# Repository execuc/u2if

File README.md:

# u2if project

u2if(USB to interfaces) is an attempt to implement some of the MicroPython "machine" module functionalities on a computer.
The goal is to be able to communicate with breakout boards (sensors, lcd...) simply from a python program on x86 machine. It uses a Raspberry PICO (or other RP2040 based board) to make the interface between the computer (USB) and peripherals/protocols.

**Python led swith on/off**:
```python
import time
from machine import u2if, Pin

# Initialize GPIO to output and set the value HIGH
led = Pin(u2if.GP3, Pin.OUT, value=Pin.HIGH)
time.sleep(1)
# Switch off the led
led.value(Pin.LOW)
```

## Caution

It is in experimental state and not everything has been tested. Use with caution. It is supposed to work on windows, linux and Mac.
To work in Linux in non-root, an udev rules has to be added (See [Firmware readme](firmware/README.md)).

## Why this project ?
When I want to retrieve values from a sensor or even to play with a led or a button from the PC, I make an arduino program that communicate to the PC via the serial port. That umplies to define a serial "protocol" between the PC and the arduino and it is not necessarily reusable because it is specific. I find it interesting to implement a majority of the functionalities of the MicroPython machine module and add other protocols.

Solutions already exist, for example [Adafruit Blinka](https://github.com/adafruit/Adafruit_Blinka) from Adafruit via the FT2232H in CircuitPython or pyftdi in Python with the same IC.
Note: now, firmware part can be also used with Adafruit Blinka ! 

## Implemented Interfaces
The following features are coded:

* machine.Pin: input (+irq, +debounced), output (+pull down/up) and grouped pins.
* machine.Signal
* machine.ADC: read (12bits)
* machine.UART
* machine.I2C
* machine.SPI
* machine.PWM
* I2S
* WS2812B led (https://youtu.be/WCGI4C6nZ-o)
* HUB75 (https://youtu.be/qRShI9y964Q)

## Licenses and Project directories
This repository is presented as the sources of a python project ([License](source/LICENSE)).
But it also contains the following projects:

 * [firmware](firmware/): PICO firmware, binary and C++ source [License](firmware/source/LICENSE).
 * [examples](examples/): Python program examples.
 * [board](board/): Example of a pico headers board for this project  ([License](firmware/source/LICENSE)).

## How to use it

### Upload firmware
See [Firmware README](firmware/README.md)

### Install u2if python package

Install python package from release file (u2if-*.*.tar.gz) with python3 -m pip install dist/u2if-*.*.tar.gz

## Build u2if python package

To build package if wanted :

 * If needed, install build: python3 -m pip install --upgrade build
 * Build it: python3 -m build

### Examples

There is no documentation but [examples](examples/) can help to use this library :

 * Led On/Off
 * Switch with or whithour irq and debouncing
 * PWM controlling servo-motor
 * Display testing: SSD1306 (I2C and SPI), GC9A01 (round lcd)
 * Some sensors simple test: MPU9250 (IMU), VL53L0X (range), BMP280(Temp)
 * UART read/Write
 * Analog read.
 * Rotrary encoder
 * I2C scan
 * Play 48khz 16bit .wav over I2S DAC (PAM5102)
 * ...

## u2if boards/pinout

For simplicity, the pins of the SPI, I2C and UART devices have been fixed. If a peripheral is not used, its pins can be used as a classic I/O. Here are the compatibles boards.

### PICO
<details>

Implemented interfaces:
 - GPIO
 - ADC
 - PWM
 - UART0 & UART1
 - I2C0 & I2C1
 - SPI0 & SPI1
 - WS2812B
 - I2S

</details>

### Adafruit Feather RP2040
<details>

Implemented interfaces:
 - GPIO
 - ADC
 - PWM
 - UART0
 - I2C0 & I2C1
 - SPI0 & SPI1
 - WS2812B

</details>

### Adafruit Qt Py RP2040
<details>

Implemented interfaces:
 - GPIO
 - ADC
 - PWM
 - UART1
 - I2C0 & I2C1
 - SPI0
 - WS2812B

</details>

### Adafruit ItsyBitsy RP2040
<details>

Implemented interfaces:
 - GPIO
 - ADC
 - PWM
 - UART0
 - I2C1
 - SPI0 & SPI1
 - WS2812B

</details>

### Adafruit MacroPad RP2040
<details>

Implemented interfaces:
 - GPIO
 - PWM
 - UART1
 - I2C0
 - SPI1
 - WS2812B

</details>

### Adafruit Trinkey QT2040
<details>

Implemented interfaces:
 - GPIO
 - ADC
 - PWM
 - UART0
 - I2C0 & I2C1
 - SPI0 & SPI1
 - WS2812B

</details>

## Troubleshooting
### Import error using MicroPython module
#### import ustruct

The ustruct module is belongs by micropython. There is a micropython-cpython-ustruct compatibility module, but it doesn't seem to work for me. If necessary modify:
```python
import ustruct
```
to:
```python
import struct as ustruct
```

#### import utime & const

Install micropython-cpython-utime and micropython-cpython-micropython.

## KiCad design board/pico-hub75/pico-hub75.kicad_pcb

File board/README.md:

# PICO headers dev board

There are some kicad projects of a PCB with some I/O but mostly headers.
**Caution**: I am not an electronic engineer, check schematics and PCB before using it !

## pico-dev-v2
Dev. board with headers.

Zipped gerber file is available: [Gerber file](pico-dev/gerber/pico-dev-v2.zip)

## pico-dev-hub75
Dev. board with hub75 connector. Caution, there is no level translator (3.3v -> 5V), so it may not work with some leds matrix because of they work on 5V logic level.

There are two jumpers to wire D and E signal in case of 1/16 and 1/32 panels.

Zipped gerber file is available: [Gerber file](pico-hub75/gerber/pico-hub75.zip)

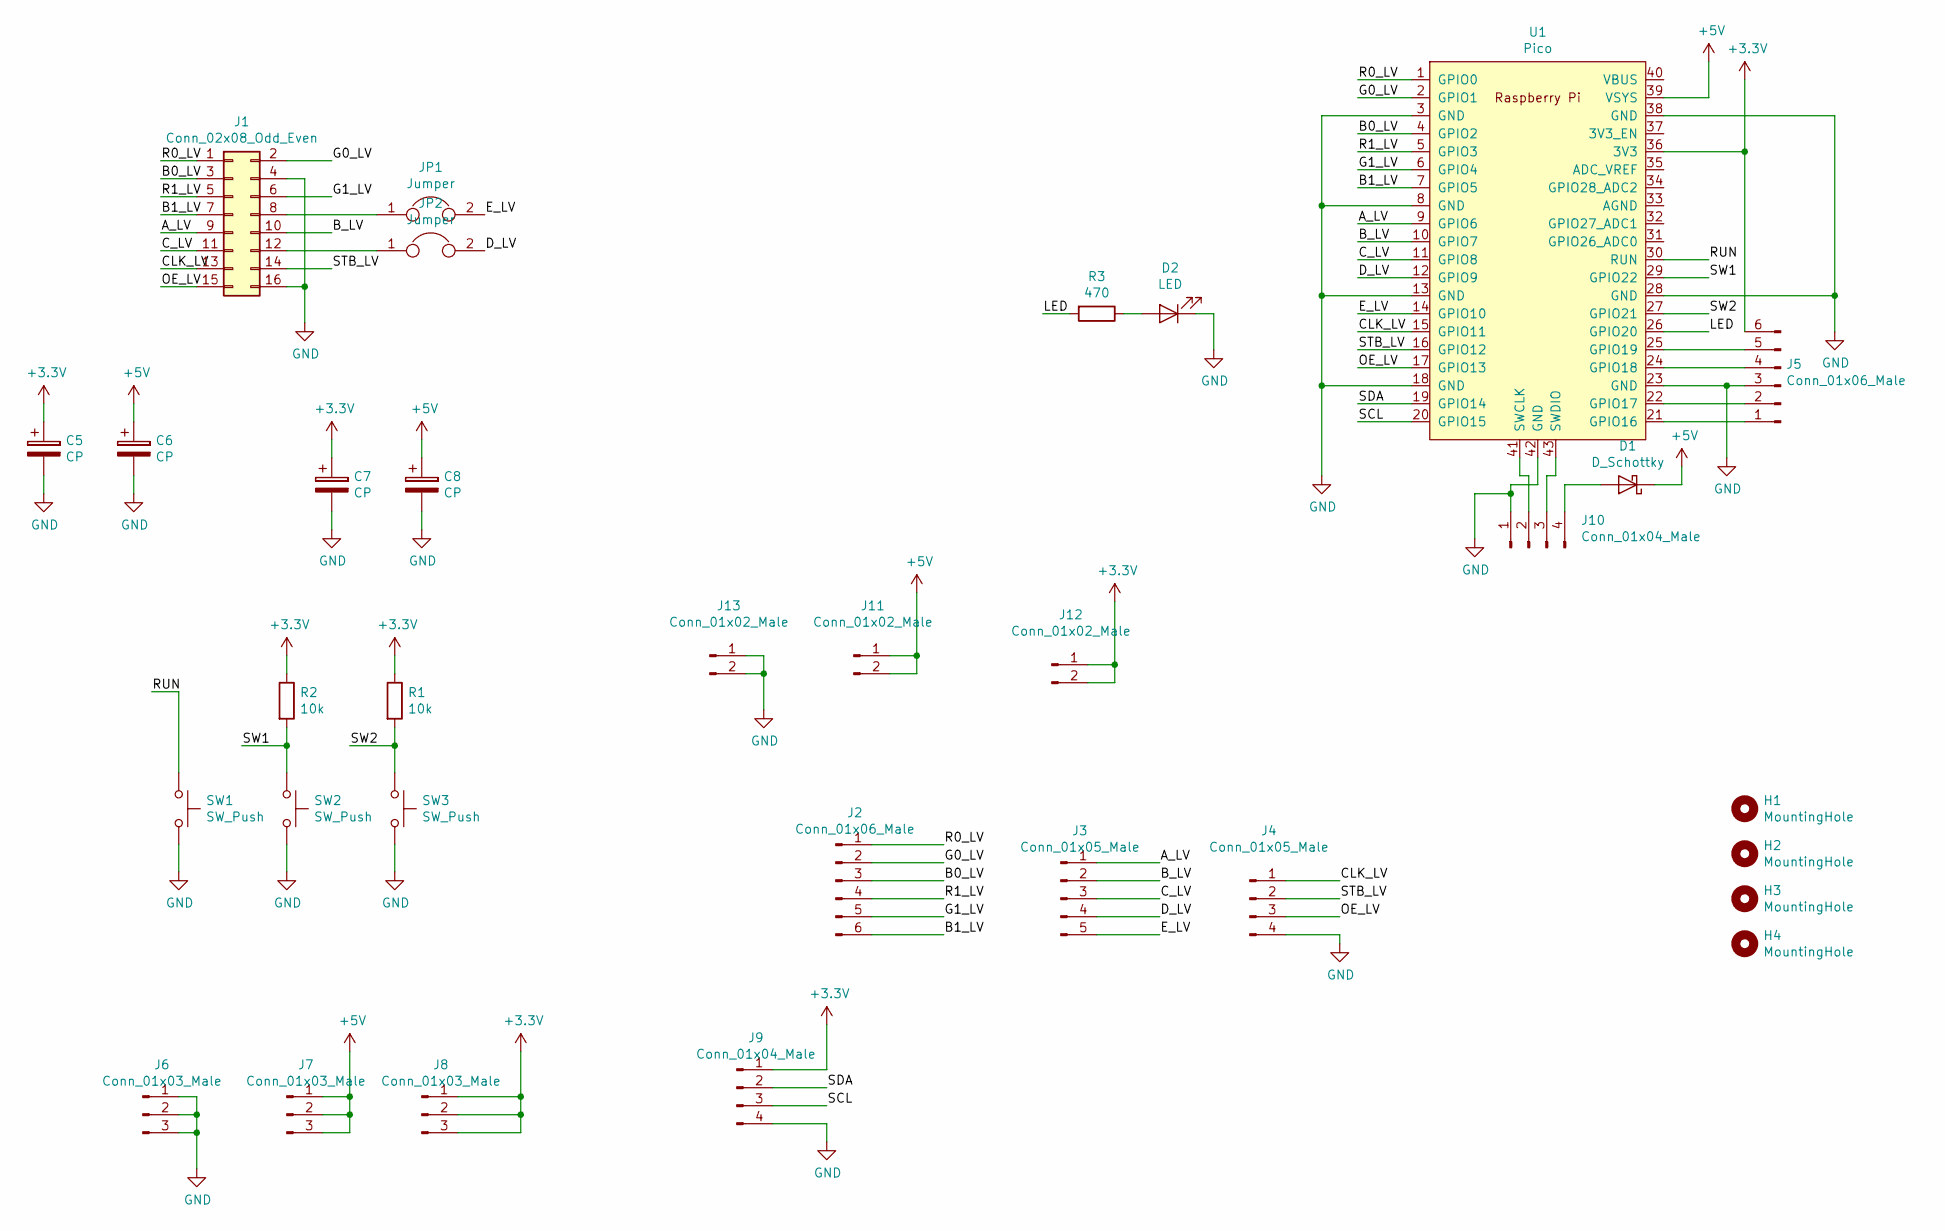
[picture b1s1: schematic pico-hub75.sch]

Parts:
C5, C6, C7, C8: CP; CP_Radial_D6.3mm_P2.50mm
D1: D_Schottky; D_SMA
D2: LED; LED_1206_3216Metric_Pad1.42x1.75mm_HandSolder; LCSC C2296
H1, H2, H3, H4: MountingHole; MountingHole_3.2mm_M3
J1: Conn_02x08_Odd_Even; IDC-Header_2x08_P2.54mm_Vertical
J2, J5: Conn_01x06_Male; PinHeader_1x06_P2.54mm_Vertical
J3: Conn_01x05_Male; PinHeader_1x05_P2.54mm_Vertical
J4: Conn_01x05_Male; PinHeader_1x04_P2.54mm_Vertical
J6, J7, J8: Conn_01x03_Male; PinHeader_1x03_P2.54mm_Vertical
J9, J10: Conn_01x04_Male; PinHeader_1x04_P2.54mm_Vertical
J11, J12, J13: Conn_01x02_Male; PinHeader_1x02_P2.54mm_Vertical
JP1, JP2: Jumper; PinHeader_1x02_P2.54mm_Vertical
R1, R2: 10k; R_1206_3216Metric_Pad1.42x1.75mm_HandSolder; LCSC C17414
R3: 470; R_1206_3216Metric_Pad1.42x1.75mm_HandSolder; LCSC C17710
SW1, SW2, SW3: SW_Push; SW_PUSH_6mm_H5mm
U1: Pico; RPi_Pico_SMD_TH

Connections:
+3V3: C5.1, C7.1, J5.6, J8.1, J8.2, J8.3, J9.1, J12.1, J12.2, R1.1, R2.1, U1.36 (3V3); also elsewhere on the board
+5V: C6.1, C8.1, D1.1 (K), J7.1, J7.2, J7.3, J11.1, J11.2, U1.39 (VSYS); also elsewhere on the board
/A_LV: J1.9, J3.1, U1.9 (GPIO6)
/B0_LV: J1.3, J2.3, U1.4 (GPIO2)
/B1_LV: J1.7, J2.6, U1.7 (GPIO5)
/B_LV: J1.10, J3.2, U1.10 (GPIO7)
/CLK_LV: J1.13, J4.1, U1.15 (GPIO11)
/C_LV: J1.11, J3.3, U1.11 (GPIO8)
/D_LV: J3.4, JP2.2, U1.12 (GPIO9)
/E_LV: J3.5, JP1.2, U1.14 (GPIO10)
/G0_LV: J1.2, J2.2, U1.2 (GPIO1)
/G1_LV: J1.6, J2.5, U1.6 (GPIO4)
/LED: R3.2, U1.26 (GPIO20)
/OE_LV: J1.15, J4.3, U1.17 (GPIO13)
/R0_LV: J1.1, J2.1, U1.1 (GPIO0)
/R1_LV: J1.5, J2.4, U1.5 (GPIO3)
/RUN: SW1.1, U1.30 (RUN)
/SCL: J9.3, U1.20 (GPIO15)
/SDA: J9.2, U1.19 (GPIO14)
/STB_LV: J1.14, J4.2, U1.16 (GPIO12)
/SW1: R2.2, SW2.1, U1.29 (GPIO22)
/SW2: R1.2, SW3.1, U1.27 (GPIO21)
GND: C5.2, C6.2, C7.2, C8.2, D2.1 (K), J1.4, J1.16, J4.4, J5.3, J6.1, J6.2, J6.3, J9.4, J10.1, J13.1, J13.2, SW1.2, SW2.2, SW3.2, U1.3 (GND), U1.8 (GND), U1.13 (GND), U1.18 (GND), U1.23 (GND), U1.28 (GND), U1.38 (GND), U1.42 (GND); also elsewhere on the board
unnamed: D1.2 (A), J10.4
unnamed: D2.2 (A), R3.1
unnamed: J1.8, JP1.1
unnamed: J1.12, JP2.1
unnamed: J5.1, U1.21 (GPIO16)
unnamed: J5.2, U1.22 (GPIO17)
unnamed: J5.4, U1.24 (GPIO18)
unnamed: J5.5, U1.25 (GPIO19)
unnamed: J10.2, U1.41 (SWCLK)
unnamed: J10.3, U1.43 (SWDIO)

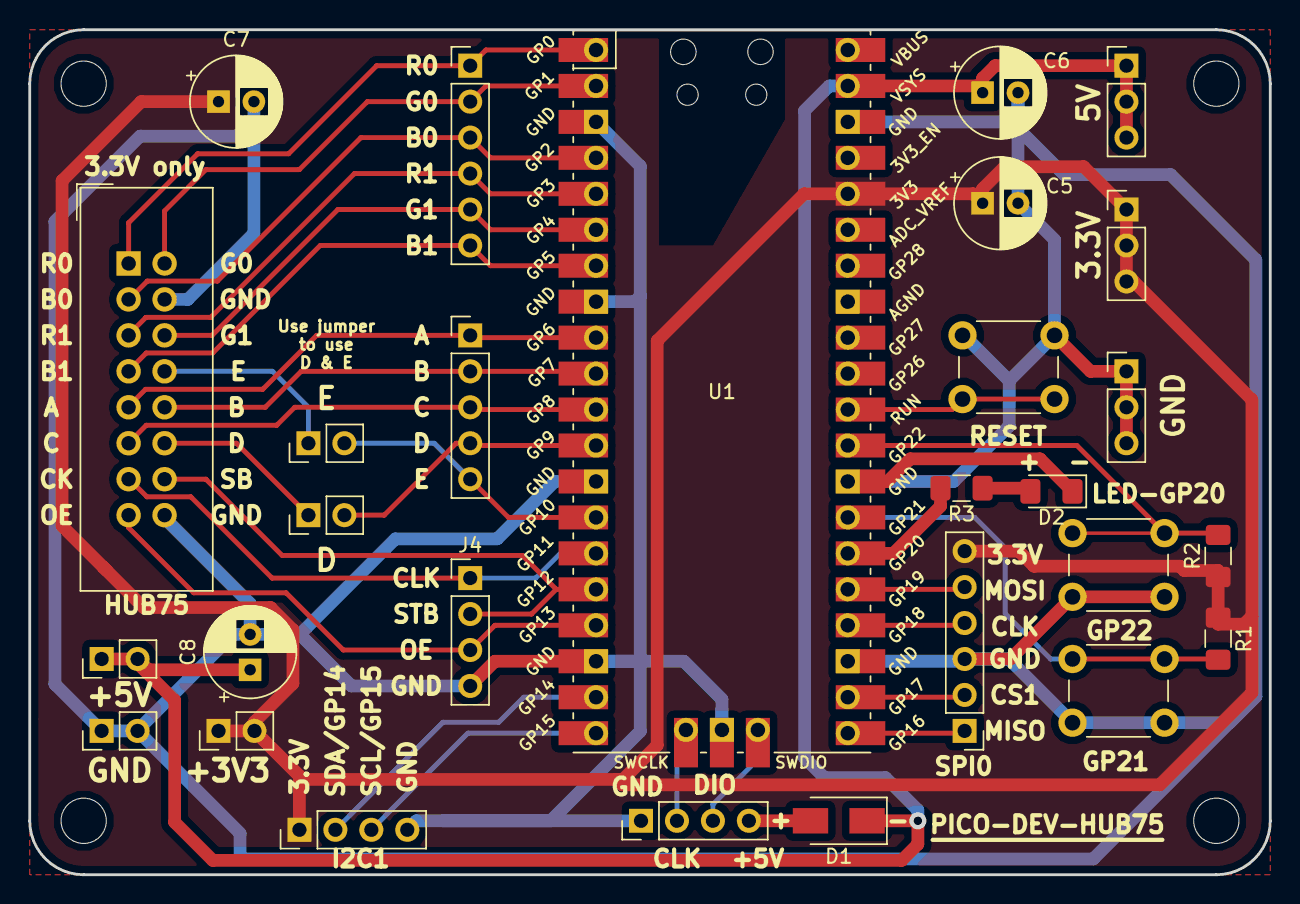
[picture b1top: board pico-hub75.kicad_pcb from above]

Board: 2 copper layers, 87.6 x 59.7 mm, 32 parts (0 on the bottom side), 33 nets.

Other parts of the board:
+3V3, +5V: Conn_01x02_Male; PinHeader_1x02_P2.54mm_Vertical
GND: Conn_01x02_Male; PinHeader_1x02_P2.54mm_Vertical

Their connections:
+3V3: +3V3.1, +3V3.2; also elsewhere on the board
+5V: +5V.1, +5V.2; also elsewhere on the board
GND: GND.1, GND.2; also elsewhere on the board

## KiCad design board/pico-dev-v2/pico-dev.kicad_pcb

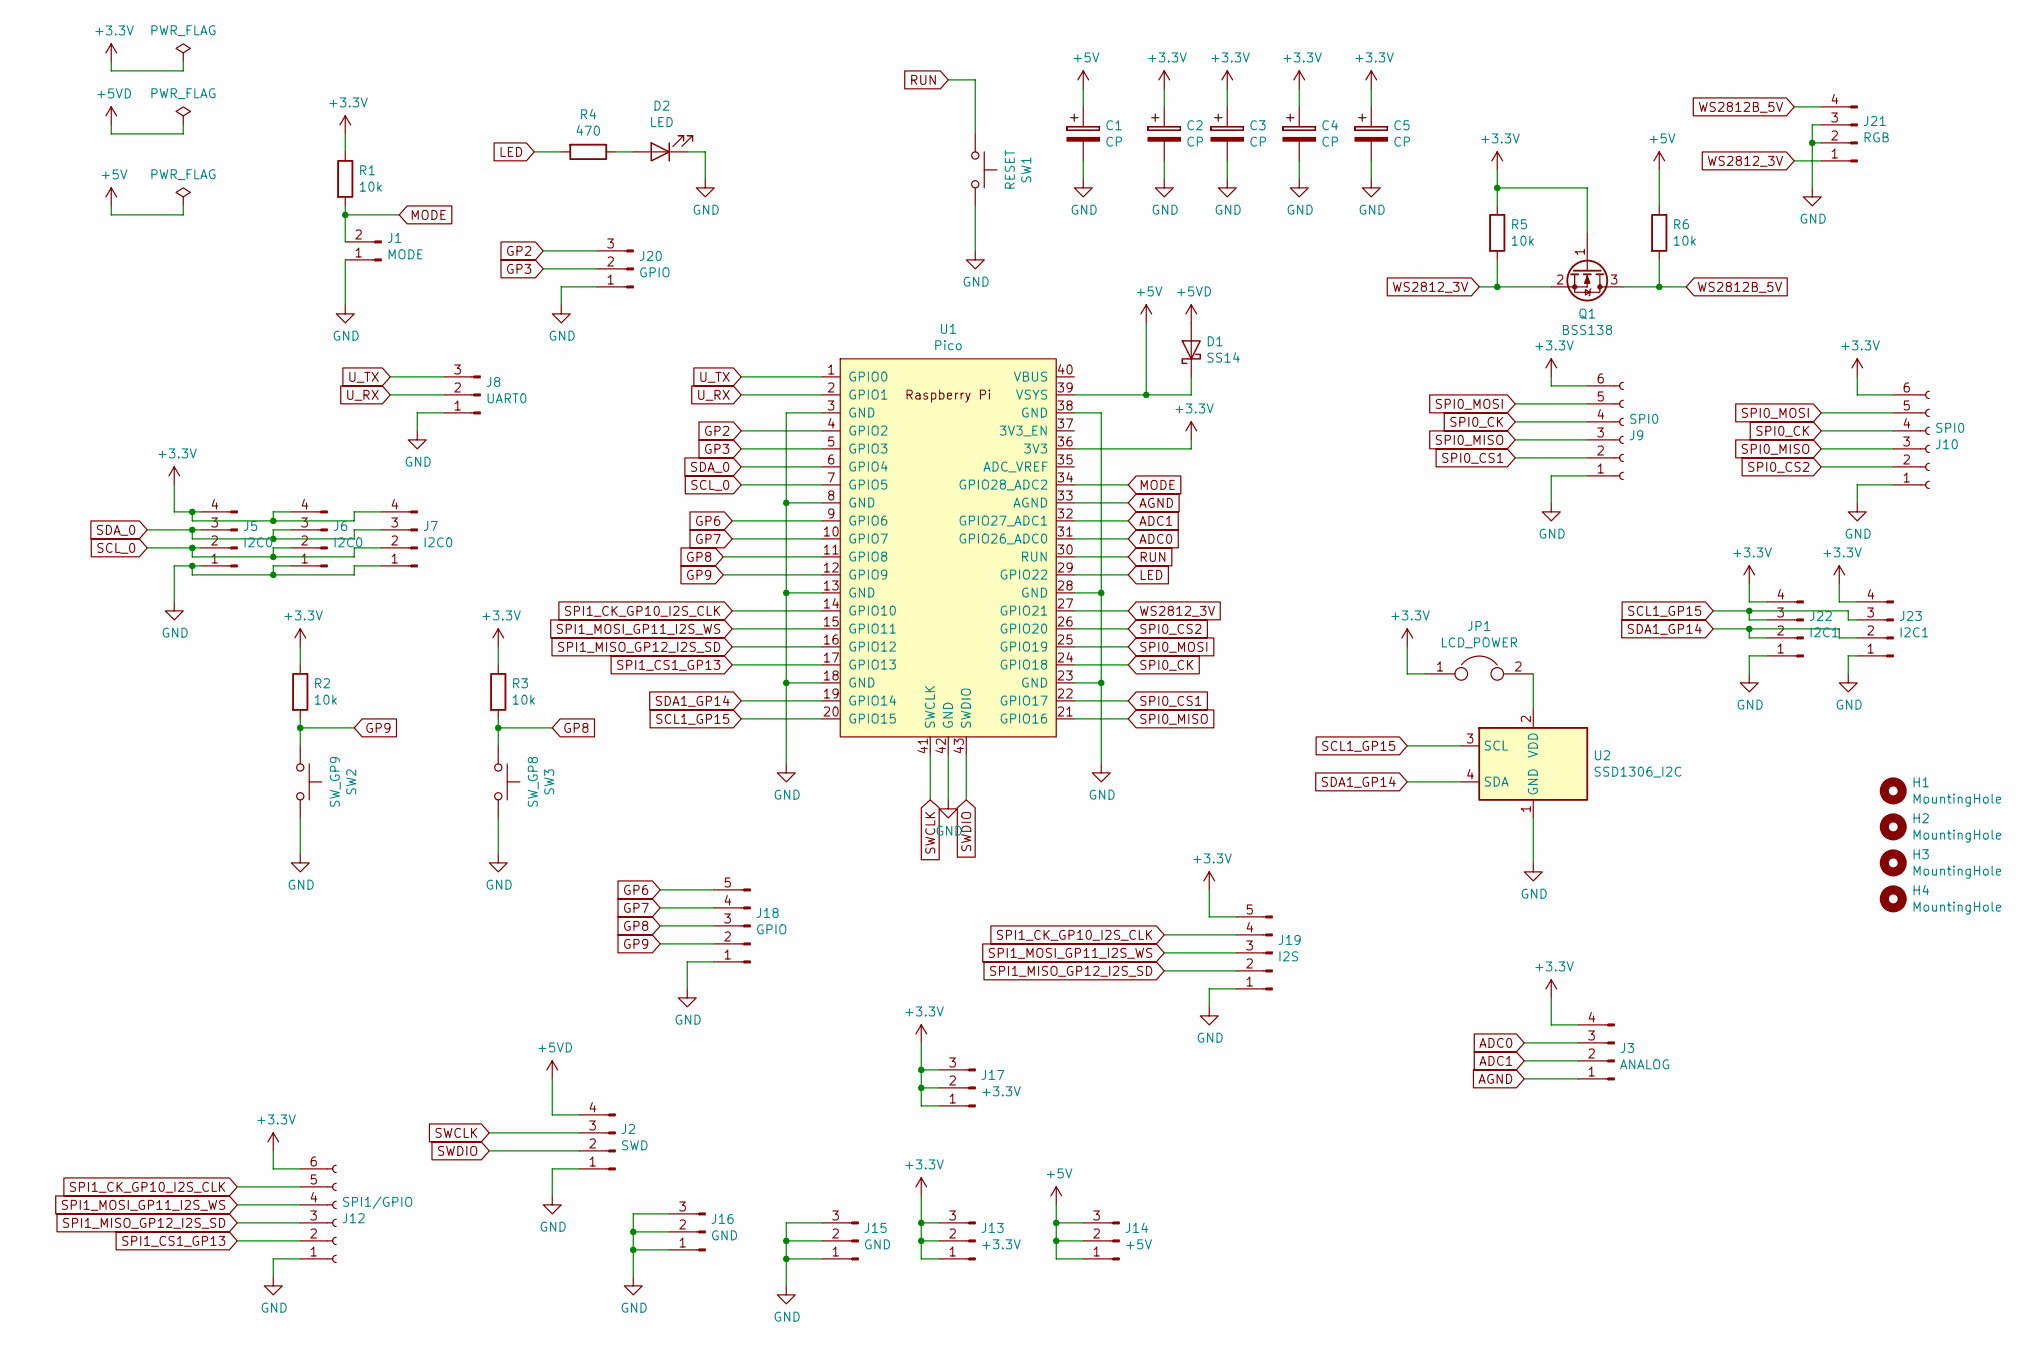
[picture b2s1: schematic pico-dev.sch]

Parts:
C1: CP; CP_Radial_D8.0mm_P3.50mm
C2, C3, C4, C5: CP; CP_Radial_D6.3mm_P2.50mm
D1: SS14; D_SMA
D2: LED; LED_1206_3216Metric_Pad1.42x1.75mm_HandSolder
H1, H2, H3, H4: MountingHole; MountingHole_3.2mm_M3
J1: MODE; PinHeader_1x02_P2.54mm_Vertical
J2: SWD; PinHeader_1x04_P2.54mm_Vertical
J3: ANALOG; PinHeader_1x04_P2.54mm_Vertical
J5, J6, J7: I2C0; PinHeader_1x04_P2.54mm_Vertical
J8: UART0; PinHeader_1x03_P2.54mm_Vertical
J9, J10: SPI0; PinHeader_1x06_P2.54mm_Vertical
J12: SPI1/GPIO; PinHeader_1x06_P2.54mm_Vertical
J13, J17: +3.3V; PinHeader_1x03_P2.54mm_Vertical
J14: +5V; PinHeader_1x03_P2.54mm_Vertical
J15, J16: GND; PinHeader_1x03_P2.54mm_Vertical
J18: GPIO; PinHeader_1x05_P2.54mm_Vertical
J19: I2S; PinHeader_1x05_P2.54mm_Vertical
J20: GPIO; PinHeader_1x03_P2.54mm_Vertical
J21: RGB; PinHeader_1x04_P2.54mm_Vertical
J22, J23: I2C1; PinHeader_1x04_P2.54mm_Vertical
JP1: LCD_POWER; PinHeader_1x02_P2.54mm_Vertical
Q1: BSS138; SOT-23_Handsoldering
R1, R2, R3, R5, R6: 10k; R_1206_3216Metric_Pad1.42x1.75mm_HandSolder
R4: 470; R_1206_3216Metric_Pad1.42x1.75mm_HandSolder
SW1: RESET; SW_PUSH_6mm_H4.3mm
SW2: SW_GP9; SW_PUSH_6mm_H4.3mm
SW3: SW_GP8; SW_PUSH_6mm_H4.3mm
U1: Pico; RPi_Pico_SMD_TH
U2: SSD1306_I2C; ssd1306_I2c

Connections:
+3V3: C2.1, C3.1, C4.1, C5.1, J3.4, J5.4, J6.4, J7.4, J9.6, J10.6, J12.6, J13.1, J13.2, J13.3, J17.1, J17.2, J17.3, J19.5, J22.4, J23.4, JP1.1, Q1.1 (G), R1.1, R2.1, R3.1, R5.1, U1.36 (3V3)
+5V: C1.1, D1.1 (K), J14.1, J14.2, J14.3, R6.1, U1.39 (VSYS)
+5VD: D1.2 (A), J2.4
ADC0: J3.3, U1.31 (GPIO26_ADC0)
ADC1: J3.2, U1.32 (GPIO27_ADC1)
AGND: J3.1, U1.33 (AGND)
GND: C1.2, C2.2, C3.2, C4.2, C5.2, D2.1 (K), J1.1, J2.1, J5.1, J6.1, J7.1, J8.1, J9.1, J10.1, J12.1, J15.1, J15.2, J15.3, J16.1, J16.2, J16.3, J18.1, J19.1, J20.1, J21.2, J21.3, J22.1, J23.1, SW1.2, SW2.2, SW3.2, U1.3 (GND), U1.8 (GND), U1.13 (GND), U1.18 (GND), U1.23 (GND), U1.28 (GND), U1.38 (GND), U1.42 (GND), U2.1 (GND)
GP2: J20.3, U1.4 (GPIO2)
GP3: J20.2, U1.5 (GPIO3)
GP6: J18.5, U1.9 (GPIO6)
GP7: J18.4, U1.10 (GPIO7)
GP8: J18.3, R3.2, SW3.1, U1.11 (GPIO8)
GP9: J18.2, R2.2, SW2.1, U1.12 (GPIO9)
LED: R4.2, U1.29 (GPIO22)
MODE: J1.2, R1.2, U1.34 (GPIO28_ADC2)
unnamed: D2.2 (A), R4.1
unnamed: JP1.2, U2.2 (VDD)
RUN: SW1.1, U1.30 (RUN)
SCL1_GP15: J22.3, J23.3, U1.20 (GPIO15), U2.3 (SCL)
SCL_0: J5.2, J6.2, J7.2, U1.7 (GPIO5)
SDA1_GP14: J22.2, J23.2, U1.19 (GPIO14), U2.4 (SDA)
SDA_0: J5.3, J6.3, J7.3, U1.6 (GPIO4)
SPI0_CK: J9.4, J10.4, U1.24 (GPIO18)
SPI0_CS1: J9.2, U1.22 (GPIO17)
SPI0_CS2: J10.2, U1.26 (GPIO20)
SPI0_MISO: J9.3, J10.3, U1.21 (GPIO16)
SPI0_MOSI: J9.5, J10.5, U1.25 (GPIO19)
SPI1_CK_GP10_I2S_CLK: J12.5, J19.4, U1.14 (GPIO10)
SPI1_CS1_GP13: J12.2, U1.17 (GPIO13)
SPI1_MISO_GP12_I2S_SD: J12.3, J19.2, U1.16 (GPIO12)
SPI1_MOSI_GP11_I2S_WS: J12.4, J19.3, U1.15 (GPIO11)
SWCLK: J2.3, U1.41 (SWCLK)
SWDIO: J2.2, U1.43 (SWDIO)
U_RX: J8.2, U1.2 (GPIO1)
U_TX: J8.3, U1.1 (GPIO0)
WS2812B_5V: J21.4, Q1.3 (D), R6.2
WS2812_3V: J21.1, Q1.2 (S), R5.2, U1.27 (GPIO21)

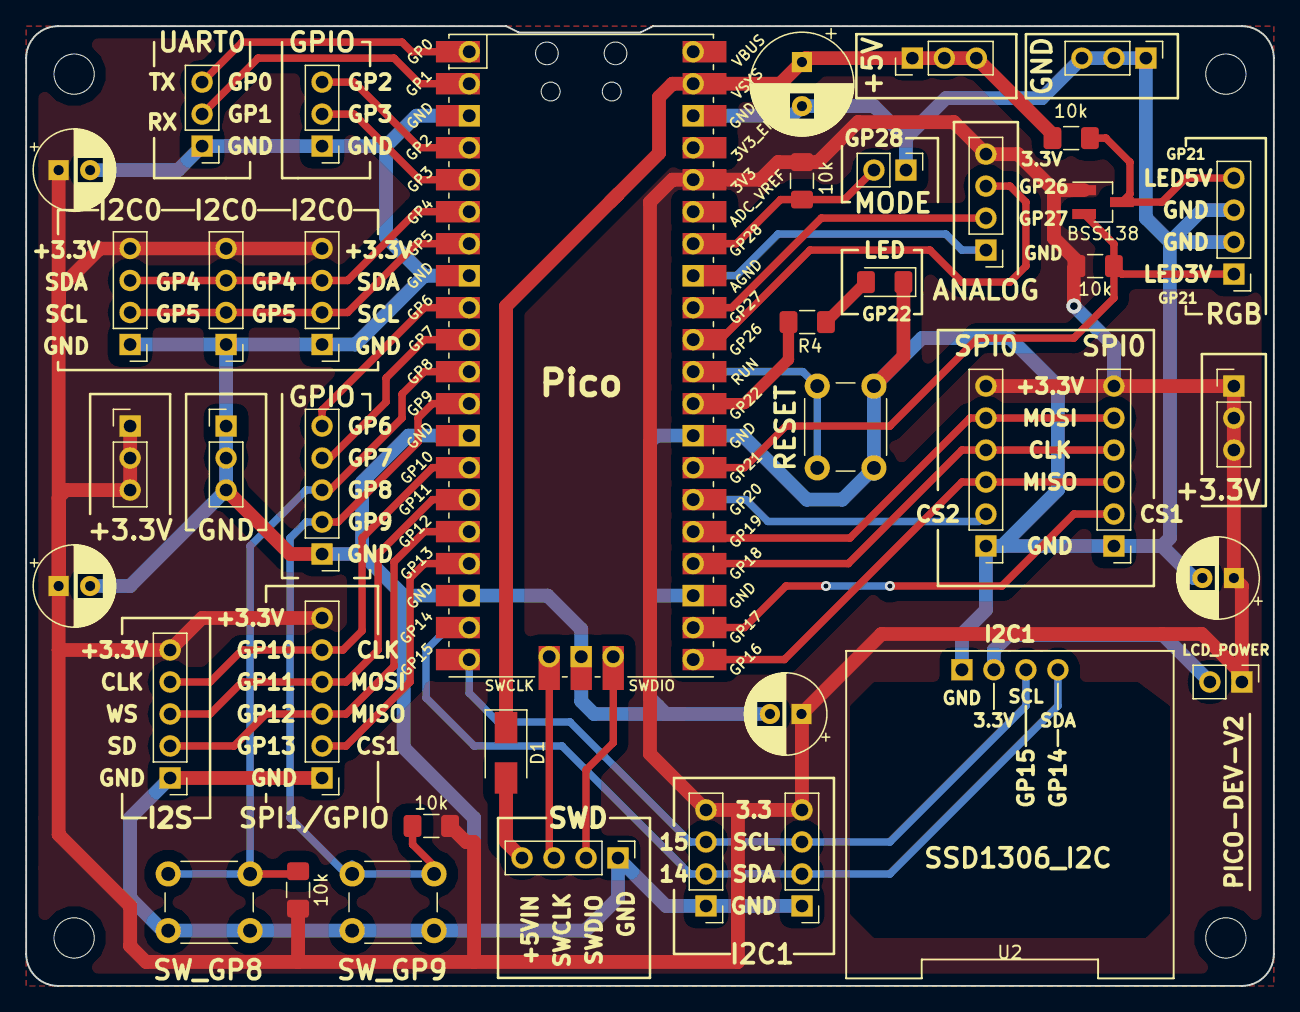
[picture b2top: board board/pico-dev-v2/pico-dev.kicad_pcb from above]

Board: 2 copper layers, 99.1 x 76.2 mm, 45 parts (0 on the bottom side), 37 nets.

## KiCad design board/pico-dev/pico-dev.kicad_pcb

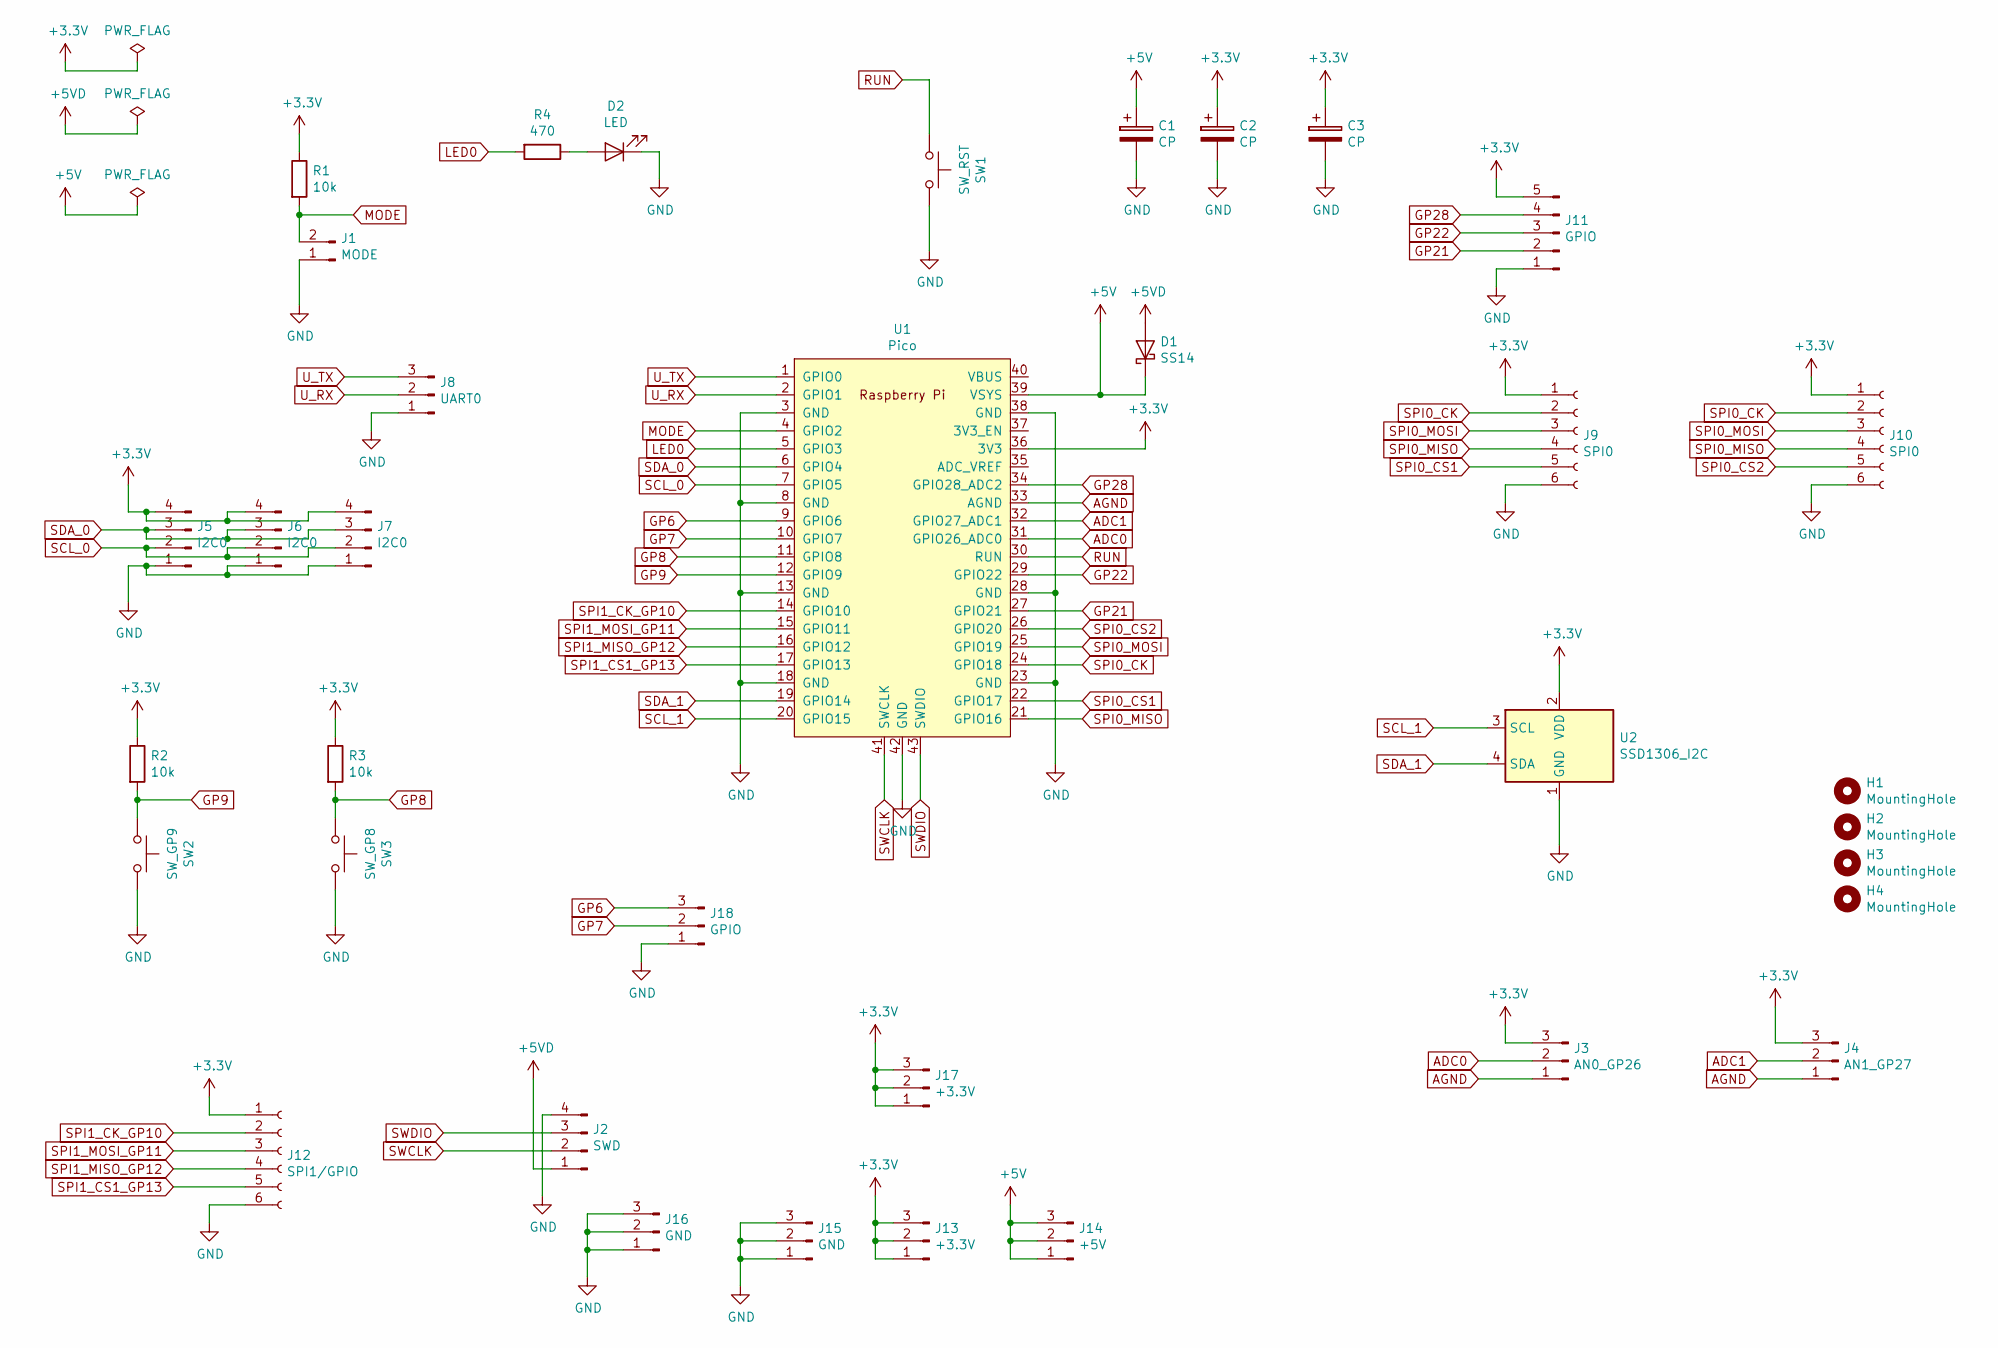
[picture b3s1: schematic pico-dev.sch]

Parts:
C1, C2, C3: CP; CP_Radial_D6.3mm_P2.50mm
D1: SS14; D_SMA
D2: LED; LED_D5.0mm
H1, H2, H3, H4: MountingHole; MountingHole_3.2mm_M3
J1: MODE; PinHeader_1x02_P2.54mm_Vertical
J2: SWD; PinHeader_1x04_P2.54mm_Vertical
J3: AN0_GP26; PinHeader_1x03_P2.54mm_Vertical
J4: AN1_GP27; PinHeader_1x03_P2.54mm_Vertical
J5, J6, J7: I2C0; PinHeader_1x04_P2.54mm_Vertical
J8: UART0; PinHeader_1x03_P2.54mm_Vertical
J9, J10: SPI0; PinHeader_1x06_P2.54mm_Vertical
J11: GPIO; PinHeader_1x05_P2.54mm_Vertical
J12: SPI1/GPIO; PinHeader_1x06_P2.54mm_Vertical
J13, J17: +3.3V; PinHeader_1x03_P2.54mm_Vertical
J14: +5V; PinHeader_1x03_P2.54mm_Vertical
J15, J16: GND; PinHeader_1x03_P2.54mm_Vertical
J18: GPIO; PinHeader_1x03_P2.54mm_Vertical
R1, R2, R3: 10k; R_0805_2012Metric_Pad1.15x1.40mm_HandSolder
R4: 470; R_0805_2012Metric_Pad1.15x1.40mm_HandSolder
SW1: SW_RST; SW_PUSH_6mm_H4.3mm
SW2: SW_GP9; SW_PUSH_6mm_H4.3mm
SW3: SW_GP8; SW_PUSH_6mm_H4.3mm
U1: Pico; RPi_Pico_SMD_TH
U2: SSD1306_I2C; ssd1306_I2c

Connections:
+3V3: C2.1, C3.1, J3.3, J4.3, J5.4, J6.4, J7.4, J9.1, J10.1, J11.5, J12.1, J13.1, J13.2, J13.3, J17.1, J17.2, J17.3, R1.1, R2.1, R3.1, U1.36 (3V3), U2.2 (VDD)
+5V: C1.1, D1.1 (K), J14.1, J14.2, J14.3, U1.39 (VSYS)
+5VD: D1.2 (A), J2.1
ADC0: J3.2, U1.31 (GPIO26_ADC0)
ADC1: J4.2, U1.32 (GPIO27_ADC1)
AGND: J3.1, J4.1, U1.33 (AGND)
GND: C1.2, C2.2, C3.2, D2.1 (K), J1.1, J2.4, J5.1, J6.1, J7.1, J8.1, J9.6, J10.6, J11.1, J12.6, J15.1, J15.2, J15.3, J16.1, J16.2, J16.3, J18.1, SW1.2, SW2.2, SW3.2, U1.3 (GND), U1.8 (GND), U1.13 (GND), U1.18 (GND), U1.23 (GND), U1.28 (GND), U1.38 (GND), U1.42 (GND), U2.1 (GND)
GP6: J18.3, U1.9 (GPIO6)
GP7: J18.2, U1.10 (GPIO7)
GP8: R3.2, SW3.1, U1.11 (GPIO8)
GP9: R2.2, SW2.1, U1.12 (GPIO9)
GP21: J11.2, U1.27 (GPIO21)
GP22: J11.3, U1.29 (GPIO22)
GP28: J11.4, U1.34 (GPIO28_ADC2)
LED0: R4.2, U1.5 (GPIO3)
MODE: J1.2, R1.2, U1.4 (GPIO2)
unnamed: D2.2 (A), R4.1
RUN: SW1.1, U1.30 (RUN)
SCL_0: J5.2, J6.2, J7.2, U1.7 (GPIO5)
SCL_1: U1.20 (GPIO15), U2.3 (SCL)
SDA_0: J5.3, J6.3, J7.3, U1.6 (GPIO4)
SDA_1: U1.19 (GPIO14), U2.4 (SDA)
SPI0_CK: J9.2, J10.2, U1.24 (GPIO18)
SPI0_CS1: J9.5, U1.22 (GPIO17)
SPI0_CS2: J10.5, U1.26 (GPIO20)
SPI0_MISO: J9.4, J10.4, U1.21 (GPIO16)
SPI0_MOSI: J9.3, J10.3, U1.25 (GPIO19)
SPI1_CK_GP10: J12.2, U1.14 (GPIO10)
SPI1_CS1_GP13: J12.5, U1.17 (GPIO13)
SPI1_MISO_GP12: J12.4, U1.16 (GPIO12)
SPI1_MOSI_GP11: J12.3, U1.15 (GPIO11)
SWCLK: J2.2, U1.41 (SWCLK)
SWDIO: J2.3, U1.43 (SWDIO)
U_RX: J8.2, U1.2 (GPIO1)
U_TX: J8.3, U1.1 (GPIO0)

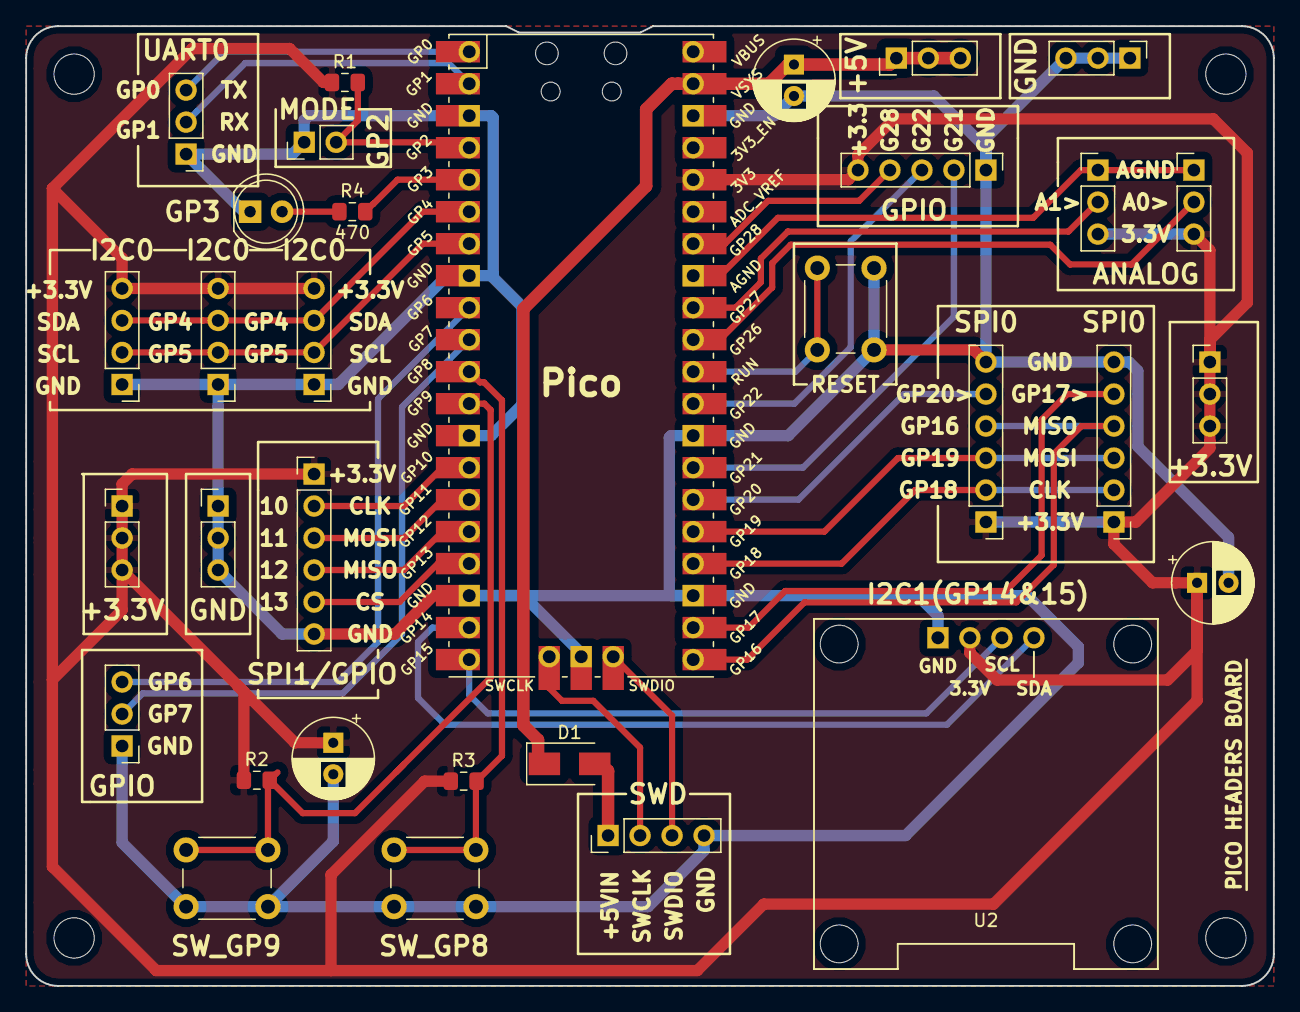
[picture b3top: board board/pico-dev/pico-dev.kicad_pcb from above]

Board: 2 copper layers, 99.1 x 76.2 mm, 36 parts (0 on the bottom side), 35 nets.

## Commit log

2021-03-25 Add WS2812B led interfaces
2021-04-02 Add I2s support
2021-04-02 Update global README
2021-04-26 Add ws2812b animation example
2021-04-26 pico-dev-v2 (pcb): Add missing silkscreen on analog header.
2021-05-14 initial working feather
2021-05-21 updates and cmake
2021-05-24 add pico-sdk as submodule; fix warnings
2021-06-04 UART1 implementation and multiple build script
2021-06-04 Fix find board by PID/VID
2021-06-04 Update version
2021-06-09 Grouped pins interface
2021-06-29 HUB75 interface
2021-10-06 initial add for macropad support
2021-10-07 update macropad PID
2022-03-19 change _i2c_scan from doing writes to a single read
    I was not able to detect VCNL4010 ambient light and proximity sensor as it will not ACK a write to an invalid internal address (address 0x00 is not valid). It will ACK to a read of an invalid address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
2023-04-06 Update board_config.h.in
    Added Seeed Xiao RP2040 and Waveshare Zero boards
2023-04-06 Update CMakeLists.txt
    Added Seeed Xiao RP2040 and Waveshare Zero boards
2023-04-06 Update usb_descriptors.c
    Added Seeed Xiao RP2040 and Waveshare Zero boards
2023-04-06 Update build-all.sh
    Added Seeed Xiao RP2040 and Waveshare Zero boards
2023-04-06 Update u2if.py
    Added Seeed Xiao RP2040 and Waveshare Zero boards
2023-07-10 Disable GPIO pull when Pin.PULL_NONE
2023-07-10 Require input pin when disabling gpio pull
2023-07-13 Fix ADC GPIO range from 26-28 to 26-29
2025-04-05 fix setup
    install package as machine, not source.machine
2025-11-07 Fix setup.py
2025-11-07 Fix mismatched method name in spi read operation
2025-11-07 Support SPI mode option
